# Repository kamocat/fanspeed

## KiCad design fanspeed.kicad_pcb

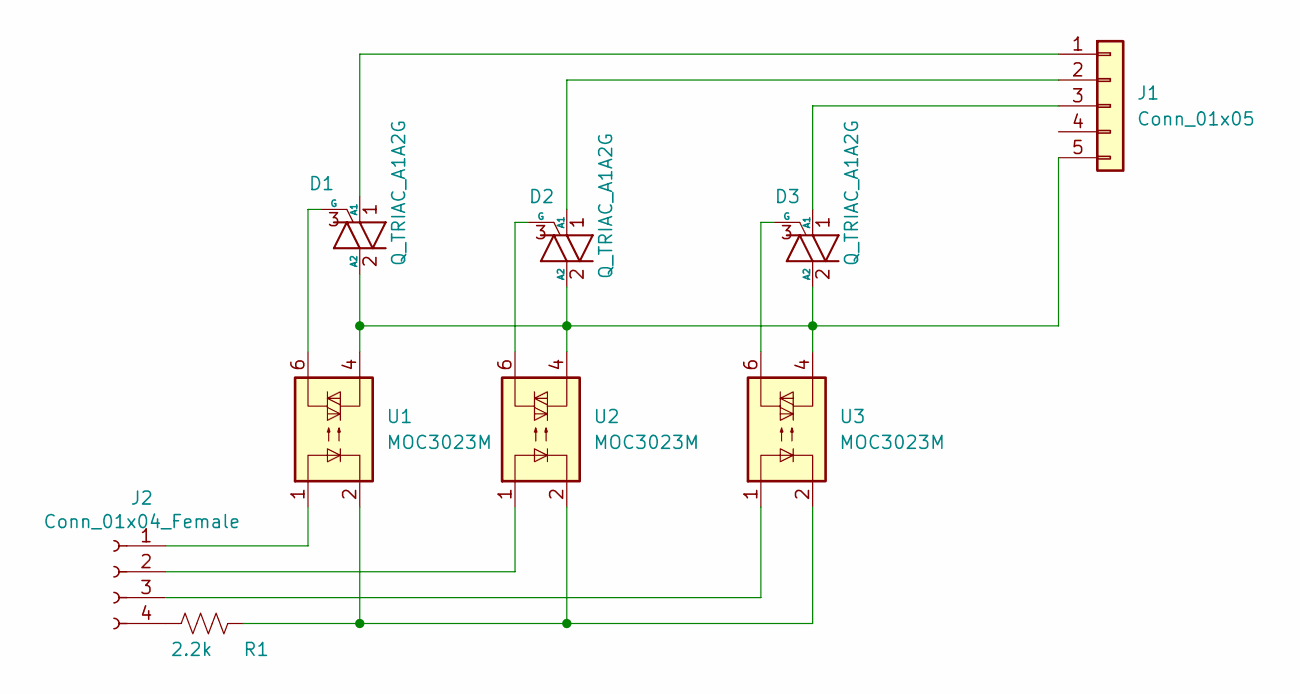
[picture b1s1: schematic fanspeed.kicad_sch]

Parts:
D1, D2, D3: Q_TRIAC_A1A2G; TO-220-3_Vertical
J1: Conn_01x05; PhoenixContact_MCV_1,5_5-G-3.5_1x05_P3.50mm_Vertical
J2: Conn_01x04_Female; PinHeader_1x04_P2.54mm_Vertical
R1: 2.2k; R_Axial_DIN0207_L6.3mm_D2.5mm_P7.62mm_Horizontal
U1, U2, U3: MOC3023M; DIP-6_W7.62mm_Socket

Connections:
unnamed: D1.1 (A1), J1.1
unnamed: D1.2 (A2), D2.2 (A2), D3.2 (A2), J1.5, U1.4, U2.4, U3.4
unnamed: D2.1 (A1), J1.2
unnamed: D3.1 (A1), J1.3
unnamed: J2.1, U1.1
unnamed: J2.2, U2.1
unnamed: J2.3, U3.1
unnamed: J2.4, R1.2
unnamed: R1.1, U1.2, U2.2, U3.2
unnamed: D1.3 (G), U1.6
unnamed: D2.3 (G), U2.6
unnamed: D3.3 (G), U3.6

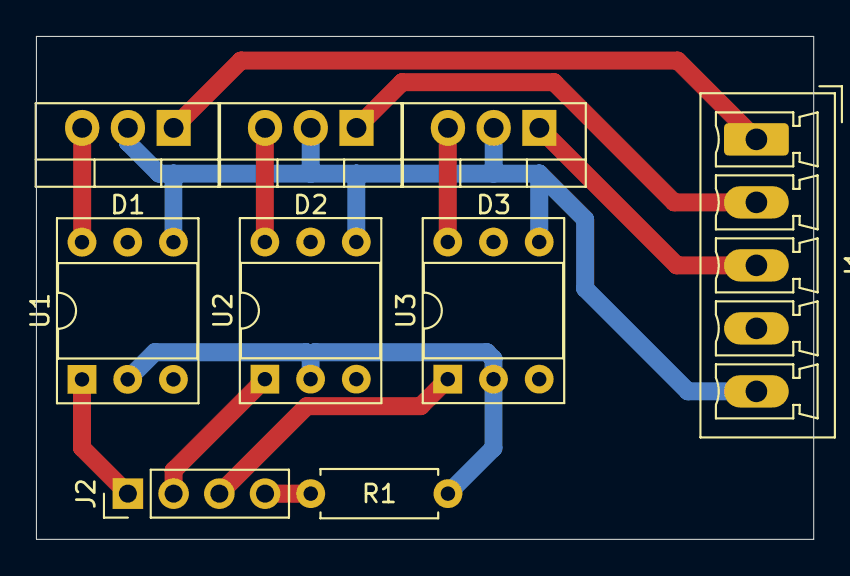
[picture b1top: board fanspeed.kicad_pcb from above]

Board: 2 copper layers, 43.2 x 27.9 mm, 9 parts (0 on the bottom side), 12 nets.

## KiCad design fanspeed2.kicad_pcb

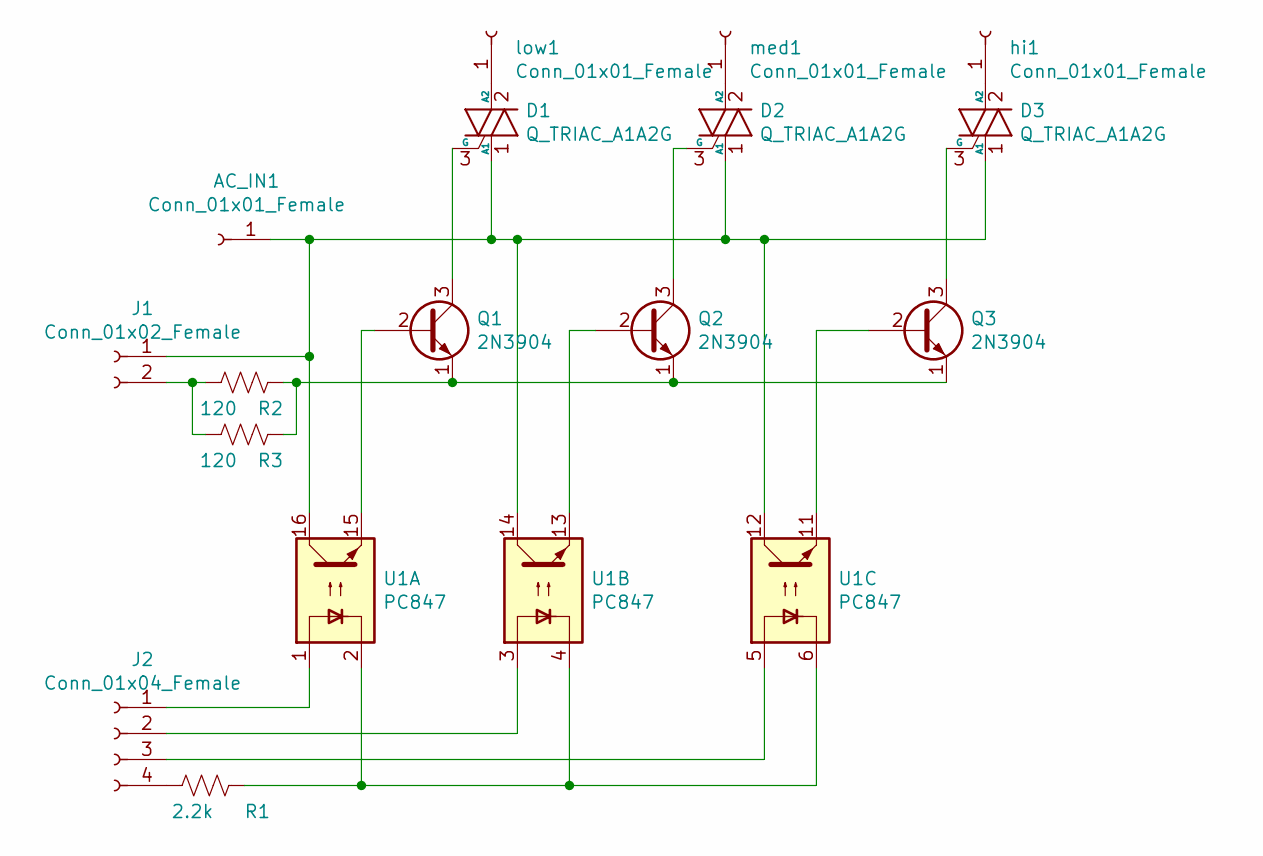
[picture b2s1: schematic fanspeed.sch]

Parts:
AC_IN1: Conn_01x01_Female; PinHeader_1x01_P2.54mm_Vertical
D1, D2, D3: Q_TRIAC_A1A2G; TO-220-3_Vertical
J1: Conn_01x02_Female; PinHeader_1x02_P2.54mm_Vertical
J2: Conn_01x04_Female; PinHeader_1x04_P2.54mm_Vertical
Q1, Q2, Q3: 2N3904; TO-92_Inline_Wide
R1: 2.2k; R_Axial_DIN0207_L6.3mm_D2.5mm_P7.62mm_Horizontal
R2, R3: 120; R_Axial_DIN0207_L6.3mm_D2.5mm_P15.24mm_Horizontal
U1: PC847; DIP-16_W7.62mm
hi1: Conn_01x01_Female; PinHeader_1x01_P2.54mm_Vertical
low1: Conn_01x01_Female; PinHeader_1x01_P2.54mm_Vertical
med1: Conn_01x01_Female; PinHeader_1x01_P2.54mm_Vertical

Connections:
unnamed: AC_IN1.1, D1.1 (A1), D2.1 (A1), D3.1 (A1), J1.1, U1.12, U1.14, U1.16
unnamed: D1.2 (A2), low1.1
unnamed: D1.3 (G), Q1.3 (C)
unnamed: D2.2 (A2), med1.1
unnamed: D2.3 (G), Q2.3 (C)
unnamed: D3.2 (A2), hi1.1
unnamed: D3.3 (G), Q3.3 (C)
unnamed: J1.2, R2.2, R3.2
unnamed: J2.1, U1.1
unnamed: J2.2, U1.3
unnamed: J2.3, U1.5
unnamed: J2.4, R1.2
unnamed: Q1.1 (E), Q2.1 (E), Q3.1 (E), R2.1, R3.1
unnamed: Q1.2 (B), U1.15
unnamed: Q2.2 (B), U1.13
unnamed: Q3.2 (B), U1.11
unnamed: R1.1, U1.2, U1.4, U1.6

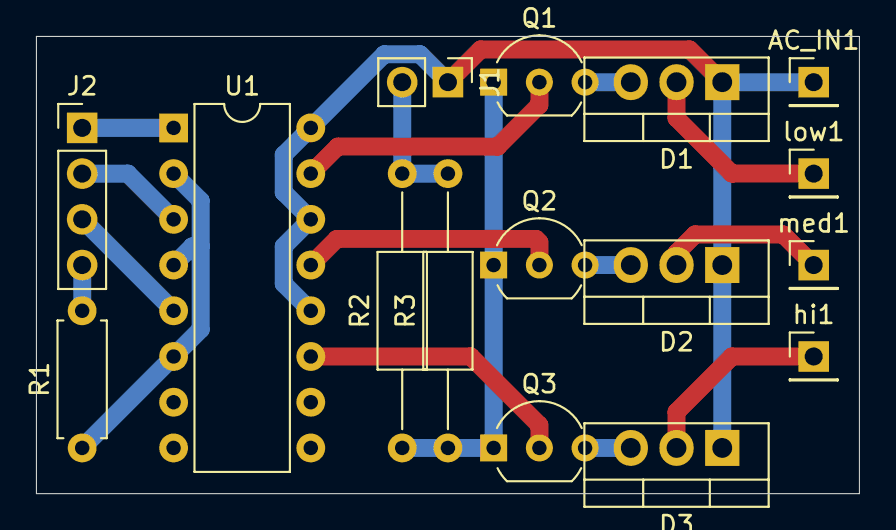
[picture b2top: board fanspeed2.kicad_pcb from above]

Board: 2 copper layers, 45.7 x 25.4 mm, 16 parts (0 on the bottom side), 17 nets.

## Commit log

2022-01-24 Switched to opto-triacs
    Upgraded KiCAD from 5 to 6
    Using the load as the current-liming resistor to simplify wiring
    Upgraded connectors to screw-terminals
